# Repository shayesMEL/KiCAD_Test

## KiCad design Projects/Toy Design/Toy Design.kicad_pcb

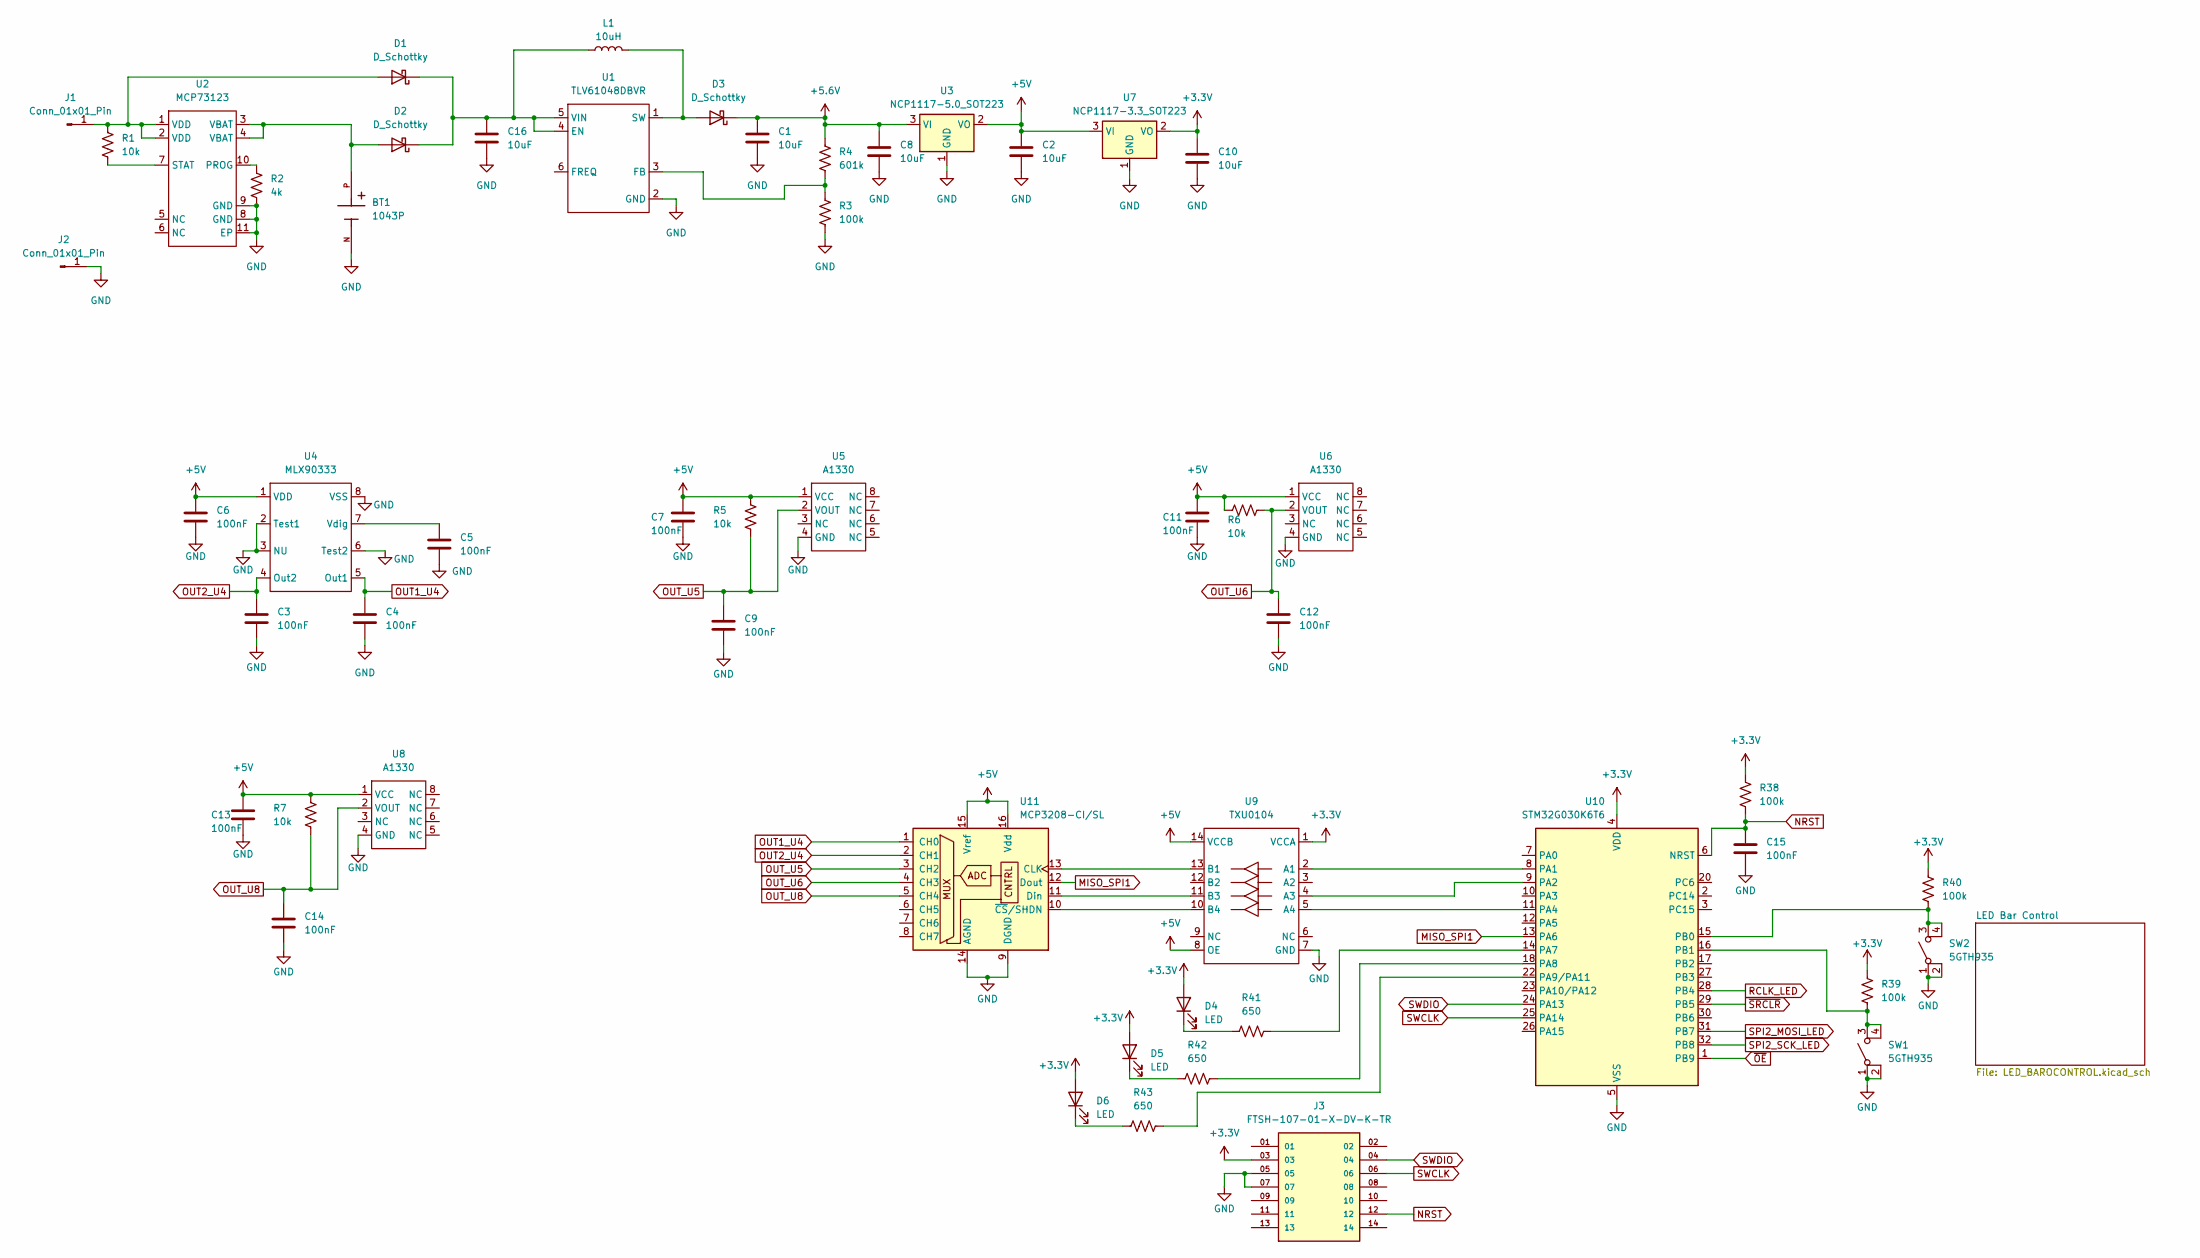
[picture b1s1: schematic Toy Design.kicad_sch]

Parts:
BT1: 1043P; BAT_1043P
C1, C2, C8, C10, C16: 10uF; C_1206_3216Metric_Pad1.33x1.80mm_HandSolder
C3, C4, C5, C6, C7, C9, C11, C12, C13, C14, C15: 100nF; C_0805_2012Metric_Pad1.18x1.45mm_HandSolder
D1, D2, D3: D_Schottky; D_SMA_Handsoldering
D4, D5, D6: LED; LED_D5.0mm
J1, J2: Conn_01x01_Pin; SolderWire-0.1sqmm_1x01_D0.4mm_OD1mm
J3: FTSH-107-01-X-DV-K-TR; SAMTEC_FTSH-107-01-X-DV-K-TR; PARTREV H
L1: 10uH; L_1210_3225Metric
R1: 10k; R_0805_2012Metric
R2: 4k; R_0805_2012Metric
R3, R38, R39, R40: 100k; R_0805_2012Metric_Pad1.20x1.40mm_HandSolder
R4: 601k; R_0805_2012Metric_Pad1.20x1.40mm_HandSolder
R5, R6, R7: 10k; R_0805_2012Metric_Pad1.20x1.40mm_HandSolder
R41, R42, R43: 650; R_0805_2012Metric_Pad1.20x1.40mm_HandSolder
SW1, SW2: 5GTH935; 5GTH9
U1: TLV61048DBVR; SOT-23-6
U2: MCP73123; DFN-10-1EP_3x3mm_P0.5mm_EP1.7x2.5mm
U3: NCP1117-5.0_SOT223; SOT-223-3_TabPin2
U4: MLX90333; SOIC-8
U5, U6, U8: A1330; TSSOP-8_4.4x3mm_P0.65mm
U7: NCP1117-3.3_SOT223; SOT-223-3_TabPin2
U9: TXU0104; TSSOP-14_4.4x5mm_P0.65mm
U10: STM32G030K6T6; LQFP-32_7x7mm_P0.8mm
U11: MCP3208-CI/SL; SOIC-16_3.9x9.9mm_P1.27mm

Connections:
+3.3V: C10.1, D4.2 (A), D5.2 (A), D6.2 (A), J3.03, R38.1, R39.1, R40.1, U7.2 (VO), U9.1 (VCCA), U10.4 (VDD); also elsewhere on the board
+5V: C2.1, C6.1, C7.1, C11.1, C13.1, R5.1, R6.1, R7.1, U3.2 (VO), U4.1 (VDD), U5.1 (VCC), U6.1 (VCC), U7.3 (VI), U8.1 (VCC), U9.8 (OE), U9.14 (VCCB), U11.15 (Vref), U11.16 (Vdd)
+6.2: C1.1, C8.1, D3.1 (K), R4.1, U3.3 (VI)
GND: BT1.N, C1.2, C2.2, C3.2, C4.2, C5.2, C6.2, C7.2, C8.2, C9.2, C10.2, C11.2, C12.2, C13.2, C14.2, C15.2, C16.2, J2.1 (Pin_1_1), J3.05, J3.07, R2.2, R3.2, SW1.1 (A), SW1.2 (B), SW2.1 (A), SW2.2 (B), U1.2 (GND), U2.8 (GND), U2.9 (GND), U2.11 (EP), U3.1 (GND), U4.2 (Test1), U4.3 (NU), U4.6 (Test2), U4.8 (VSS), U5.4 (GND), U6.4 (GND), U7.1 (GND), U8.4 (GND), U9.3 (A2), U9.7 (GND), U10.5 (VSS), U11.9 (DGND), U11.14 (AGND); also elsewhere on the board
MISO_SPI1: U10.13 (PA6), U11.12 (Dout)
NRST: C15.1, J3.12, R38.2, U10.6 (NRST)
unnamed: D1.2 (A), J1.1 (Pin_1_1), R1.1, U2.1 (VDD), U2.2 (VDD)
unnamed: C16.1, D1.1 (K), D2.1 (K), L1.1, U1.4 (EN), U1.5 (VIN)
unnamed: BT1.P, D2.2 (A), U2.3 (VBAT), U2.4 (VBAT)
unnamed: D3.2 (A), L1.2, U1.1 (SW)
unnamed: D4.1 (K), R41.1
unnamed: D5.1 (K), R42.1
unnamed: D6.1 (K), R43.1
unnamed: R3.1, R4.2, U1.3 (FB)
unnamed: R2.1, U2.10 (PROG)
unnamed: R1.2, U2.7 (STAT)
unnamed: C5.1, U4.7 (Vdig)
unnamed: U9.2 (A1), U10.8 (PA1)
unnamed: U9.4 (A3), U10.9 (PA2)
unnamed: U9.5 (A4), U10.11 (PA4)
unnamed: R41.2, U10.14 (PA7)
unnamed: R42.2, U10.18 (PA8)
unnamed: R43.2, U10.22 (PA9/PA11)
unnamed: R40.2, SW2.3 (A), SW2.4, U10.15 (PB0)
unnamed: R39.2, SW1.3 (A), SW1.4, U10.16 (PB1)
unnamed: U9.13 (B1), U11.13 (CLK)
unnamed: U9.11 (B3), U11.11 (Din)
unnamed: U9.10 (B4), U11.10 (~CS/SHDN)
OUT1_U4: C4.1, U4.5 (Out1), U11.1 (CH0)
OUT2_U4: C3.1, U4.4 (Out2), U11.2 (CH1)
OUT_U5: C9.1, R5.2, U5.2 (VOUT), U11.3 (CH2)
OUT_U6: C12.1, R6.2, U6.2 (VOUT), U11.4 (CH3)
OUT_U8: C14.1, R7.2, U8.2 (VOUT), U11.5 (CH4)
RCLK_LED: U10.28 (PB4); also elsewhere on the board
SPI2_MOSI_LED: U10.31 (PB7); also elsewhere on the board
SPI2_SCK_LED: U10.32 (PB8); also elsewhere on the board
SWCLK: J3.06, U10.25 (PA14)
SWDIO: J3.04, U10.24 (PA13)
~OE: U10.1 (PB9); also elsewhere on the board
~SRCLR: U10.29 (PB5); also elsewhere on the board

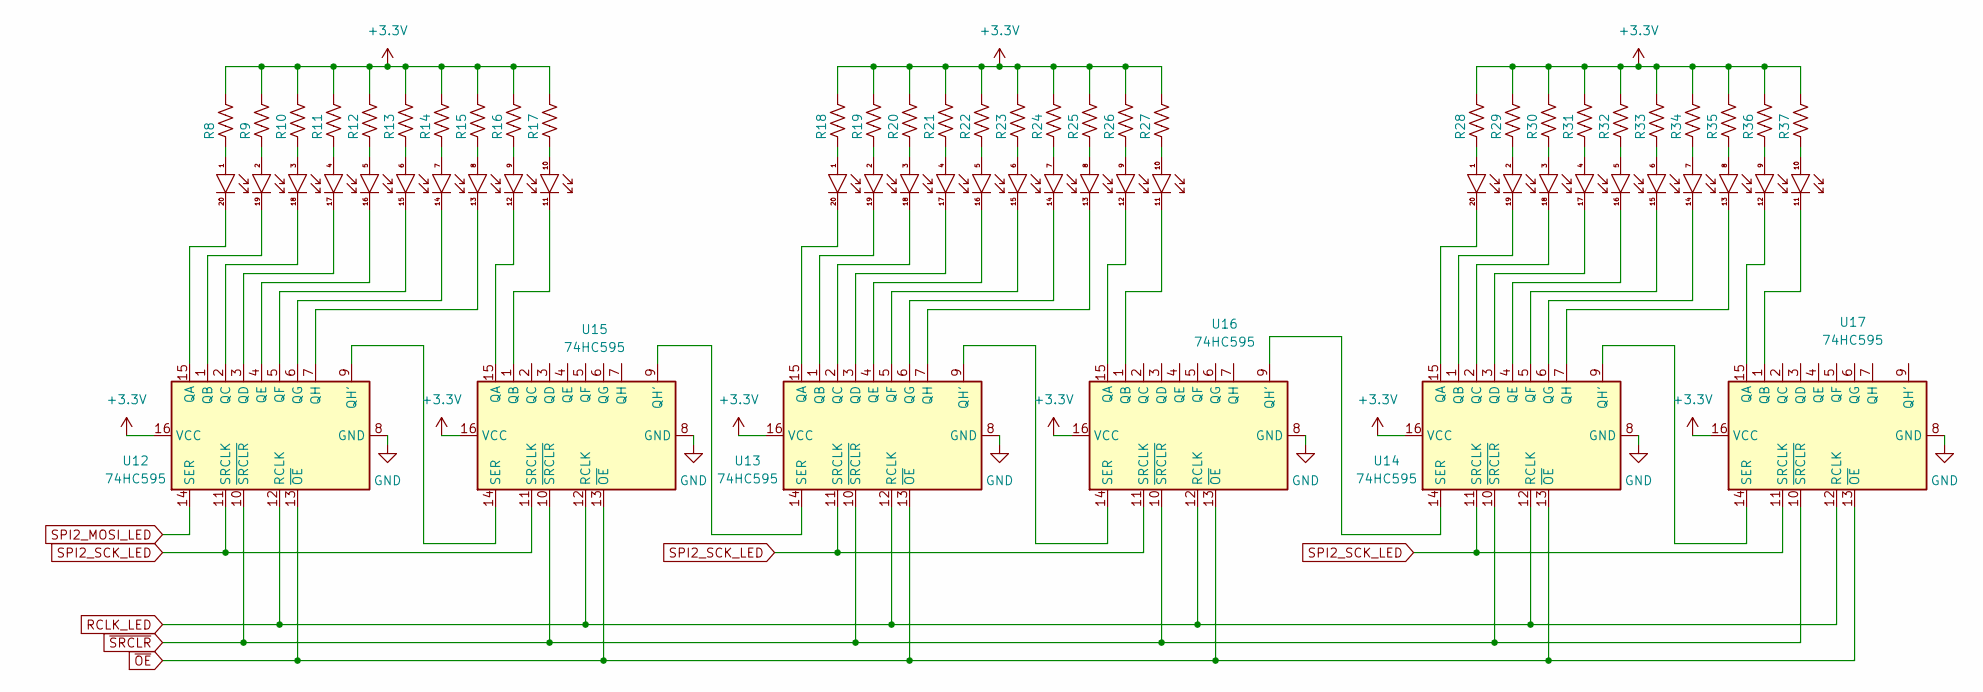
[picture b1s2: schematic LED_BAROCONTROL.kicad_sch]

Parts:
LEDB1, LEDB2, LEDB3: DIP-20_W7.62mm_LongPads
R8, R9, R10, R11, R12, R13, R14, R15, R16, R17, R18, R19, R20, R21, R22, R23, R24, R25, R26, R27, R28, R29, R30, R31, R32, R33, R34, R35, R36, R37: 1.2k; R_0805_2012Metric_Pad1.20x1.40mm_HandSolder
U12, U13, U14, U15, U16, U17: 74HC595; SOIC-16_3.9x9.9mm_P1.27mm

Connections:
+3.3V: R8.1, R9.1, R10.1, R11.1, R12.1, R13.1, R14.1, R15.1, R16.1, R17.1, R18.1, R19.1, R20.1, R21.1, R22.1, R23.1, R24.1, R25.1, R26.1, R27.1, R28.1, R29.1, R30.1, R31.1, R32.1, R33.1, R34.1, R35.1, R36.1, R37.1, U12.16 (VCC), U13.16 (VCC), U14.16 (VCC), U15.16 (VCC), U16.16 (VCC), U17.16 (VCC); also elsewhere on the board
GND: U12.8 (GND), U13.8 (GND), U14.8 (GND), U15.8 (GND), U16.8 (GND), U17.8 (GND); also elsewhere on the board
unnamed: LEDB1.1, R8.2
unnamed: LEDB1.2, R9.2
unnamed: LEDB1.3, R10.2
unnamed: LEDB1.4, R11.2
unnamed: LEDB1.5, R12.2
unnamed: LEDB1.6, R13.2
unnamed: LEDB1.7, R14.2
unnamed: LEDB1.8, R15.2
unnamed: LEDB1.9, R16.2
unnamed: LEDB1.10, R17.2
unnamed: LEDB2.1, R18.2
unnamed: LEDB2.2, R19.2
unnamed: LEDB2.3, R20.2
unnamed: LEDB2.4, R21.2
unnamed: LEDB2.5, R22.2
unnamed: LEDB2.6, R23.2
unnamed: LEDB2.7, R24.2
unnamed: LEDB2.8, R25.2
unnamed: LEDB2.9, R26.2
unnamed: LEDB2.10, R27.2
unnamed: LEDB3.1, R28.2
unnamed: LEDB3.2, R29.2
unnamed: LEDB3.3, R30.2
unnamed: LEDB3.4, R31.2
unnamed: LEDB3.5, R32.2
unnamed: LEDB3.6, R33.2
unnamed: LEDB3.7, R34.2
unnamed: LEDB3.8, R35.2
unnamed: LEDB3.9, R36.2
unnamed: LEDB3.10, R37.2
unnamed: LEDB1.20, U12.15 (QA)
unnamed: LEDB1.19, U12.1 (QB)
unnamed: LEDB1.18, U12.2 (QC)
unnamed: LEDB1.17, U12.3 (QD)
unnamed: LEDB1.16, U12.4 (QE)
unnamed: LEDB1.15, U12.5 (QF)
unnamed: LEDB1.14, U12.6 (QG)
unnamed: U12.9 (QH'), U15.14 (SER)
unnamed: LEDB1.13, U12.7 (QH)
unnamed: LEDB2.20, U13.15 (QA)
unnamed: LEDB2.19, U13.1 (QB)
unnamed: LEDB2.18, U13.2 (QC)
unnamed: LEDB2.17, U13.3 (QD)
unnamed: LEDB2.16, U13.4 (QE)
unnamed: LEDB2.15, U13.5 (QF)
unnamed: LEDB2.14, U13.6 (QG)
unnamed: U13.9 (QH'), U16.14 (SER)
unnamed: LEDB2.13, U13.7 (QH)
unnamed: U13.14 (SER), U15.9 (QH')
unnamed: LEDB3.20, U14.15 (QA)
unnamed: LEDB3.19, U14.1 (QB)
unnamed: LEDB3.18, U14.2 (QC)
unnamed: LEDB3.17, U14.3 (QD)
unnamed: LEDB3.16, U14.4 (QE)
unnamed: LEDB3.15, U14.5 (QF)
unnamed: LEDB3.14, U14.6 (QG)
unnamed: U14.9 (QH'), U17.14 (SER)
unnamed: LEDB3.13, U14.7 (QH)
unnamed: U14.14 (SER), U16.9 (QH')
unnamed: LEDB1.12, U15.15 (QA)
unnamed: LEDB1.11, U15.1 (QB)
unnamed: LEDB2.12, U16.15 (QA)
unnamed: LEDB2.11, U16.1 (QB)
unnamed: LEDB3.12, U17.15 (QA)
unnamed: LEDB3.11, U17.1 (QB)
RCLK_LED: U12.12 (RCLK), U13.12 (RCLK), U14.12 (RCLK), U15.12 (RCLK), U16.12 (RCLK), U17.12 (RCLK); also elsewhere on the board
SPI2_MOSI_LED: U12.14 (SER); also elsewhere on the board
SPI2_SCK_LED: U12.11 (SRCLK), U13.11 (SRCLK), U14.11 (SRCLK), U15.11 (SRCLK), U16.11 (SRCLK), U17.11 (SRCLK); also elsewhere on the board
~OE: U12.13 (~OE), U13.13 (~OE), U14.13 (~OE), U15.13 (~OE), U16.13 (~OE), U17.13 (~OE); also elsewhere on the board
~SRCLR: U12.10 (~SRCLR), U13.10 (~SRCLR), U14.10 (~SRCLR), U15.10 (~SRCLR), U16.10 (~SRCLR), U17.10 (~SRCLR); also elsewhere on the board

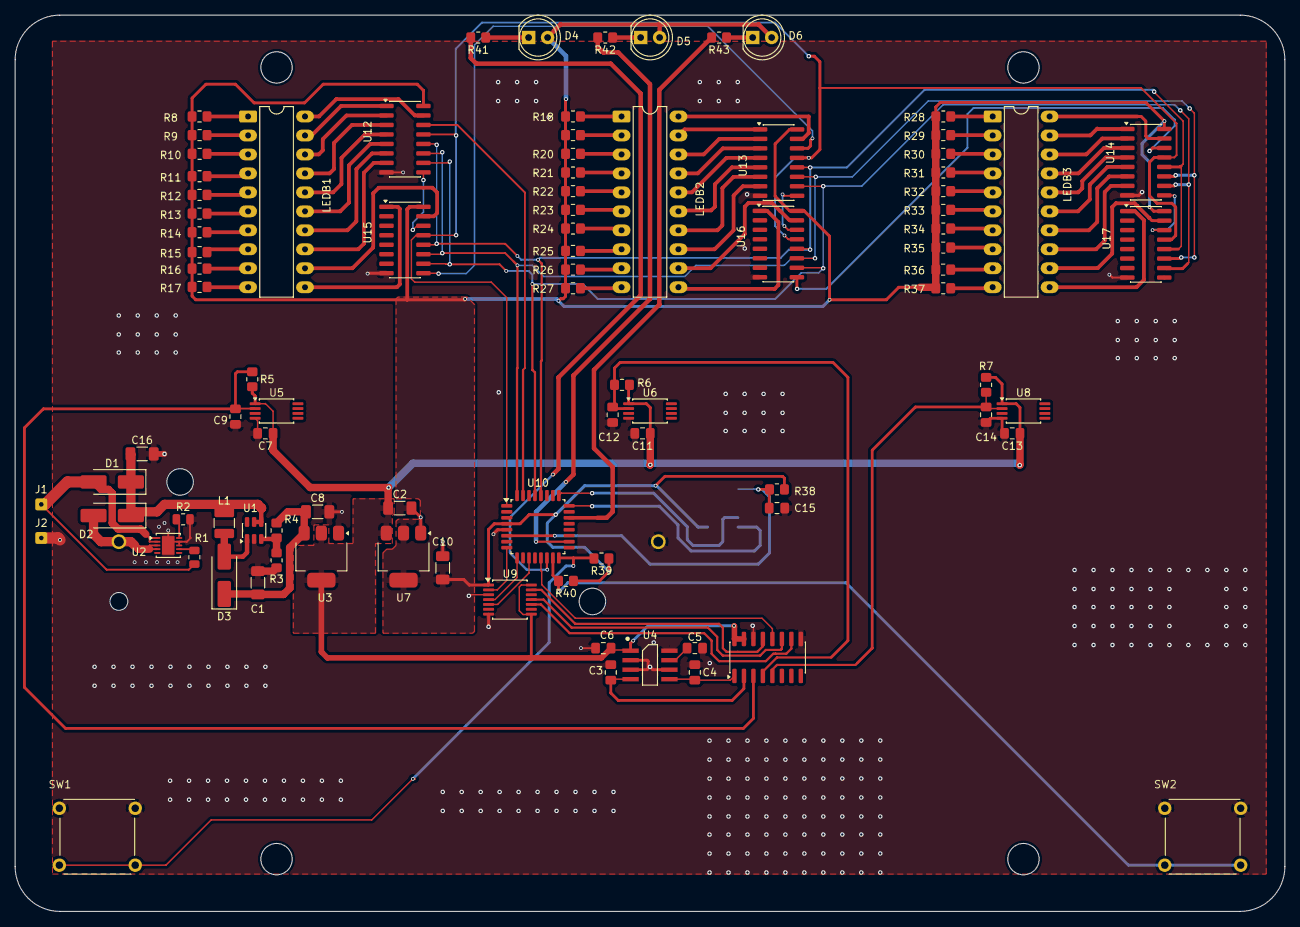
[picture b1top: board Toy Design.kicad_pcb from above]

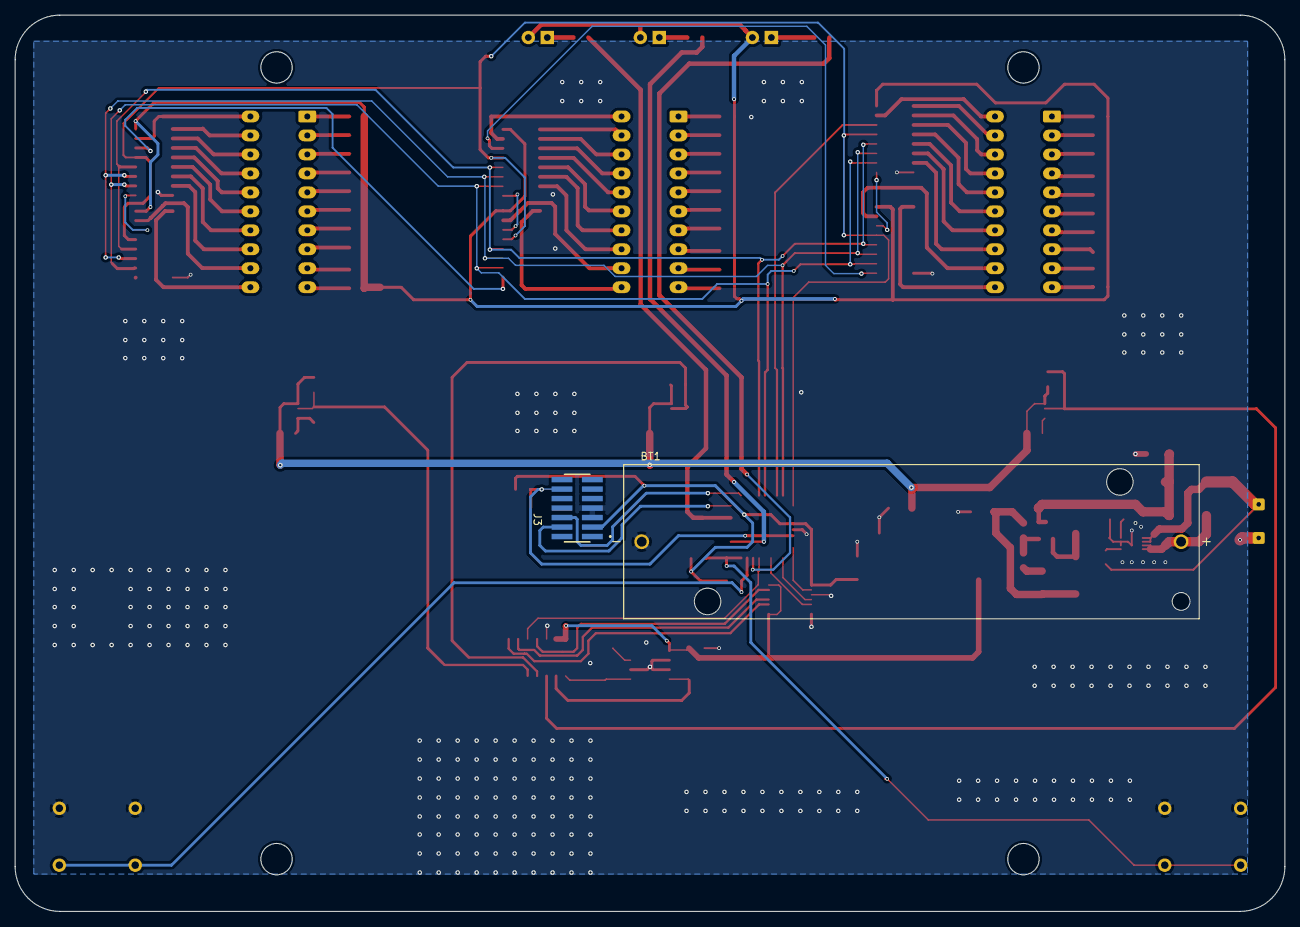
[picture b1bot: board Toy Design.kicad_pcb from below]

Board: 2 copper layers, 170.0 x 120.0 mm, 92 parts (2 on the bottom side), 105 nets.

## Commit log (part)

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2026-01-11 Initial Upload of FIles
    Init footprints
2026-03-25 added projects folder
2026-03-25 addedd mcu
2026-04-25 Updates
    Began PCB Layout and added LED controls and 3.3 to 5V level shifter
2026-05-03 LED drive and bar sch implementation
2026-05-25 started pcb post led bar
2026-05-25 Update to commit to main
2026-05-25 removed.lck for github
2026-05-25 Began routing up to te serial in parallel out ICs
2026-05-26 Finshed most signal routing
2026-05-27 90% Routing complete
2026-06-19 updated sonme stuff
2026-06-23 Updating with programmer nets but no connector YET
2026-06-24 Added connector need nets from work computer because I am an idiot
2026-06-24 Pushing connector connected to all signals
2026-06-29 Updated PCB edge to be inline with the design ifile in CLaude
